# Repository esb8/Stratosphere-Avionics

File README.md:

# Stratosphere
Stratosphere is a highly **versatile** avionics stack designed for a variety of **Remote-Controlled** (RC) vehicles such as planes, model rockets, and drones. Stratosphere is designed for *verstaility*, allowing for usage as a standalone stack and alongside off the shelf modules (VTX, GPS, etc), servos and ESCs. 

## Features
- **Flight Computer**
  - 6-axis IMU (ICM-42605)
  - High Precision Barometer (BMP388)
  - 915MHz LoRa Transciever (ELRS compatible)
  - 4 UART Outputs
  - 8 PWM capable pins
  - 4 PWM/Motor control pins (4-in-1 ESC compatible) 
  - STM32F405
  - USB-C programming
- **Power Management Unit**
  - 2-4S LiPo (7.4V-14.8V)
  - 3.3V 3A (3+ outputs)
  - 5V 3A (3+ outputs)
  - Compact + Affordable
  - XT60

## Media

**Power Management Board**

## Future Deliveries
- Update PMU connector amount (5V 3 pin to 5 pin) (4 servos + VTX).
- Power ORING/multiplexer circuit on FC.
- Layout FC
- Current Calcs

## License

This project is released under the MIT License. All design files, including schematics, PCB layouts, and firmware are open source and available for personal and commercial use with attribution.

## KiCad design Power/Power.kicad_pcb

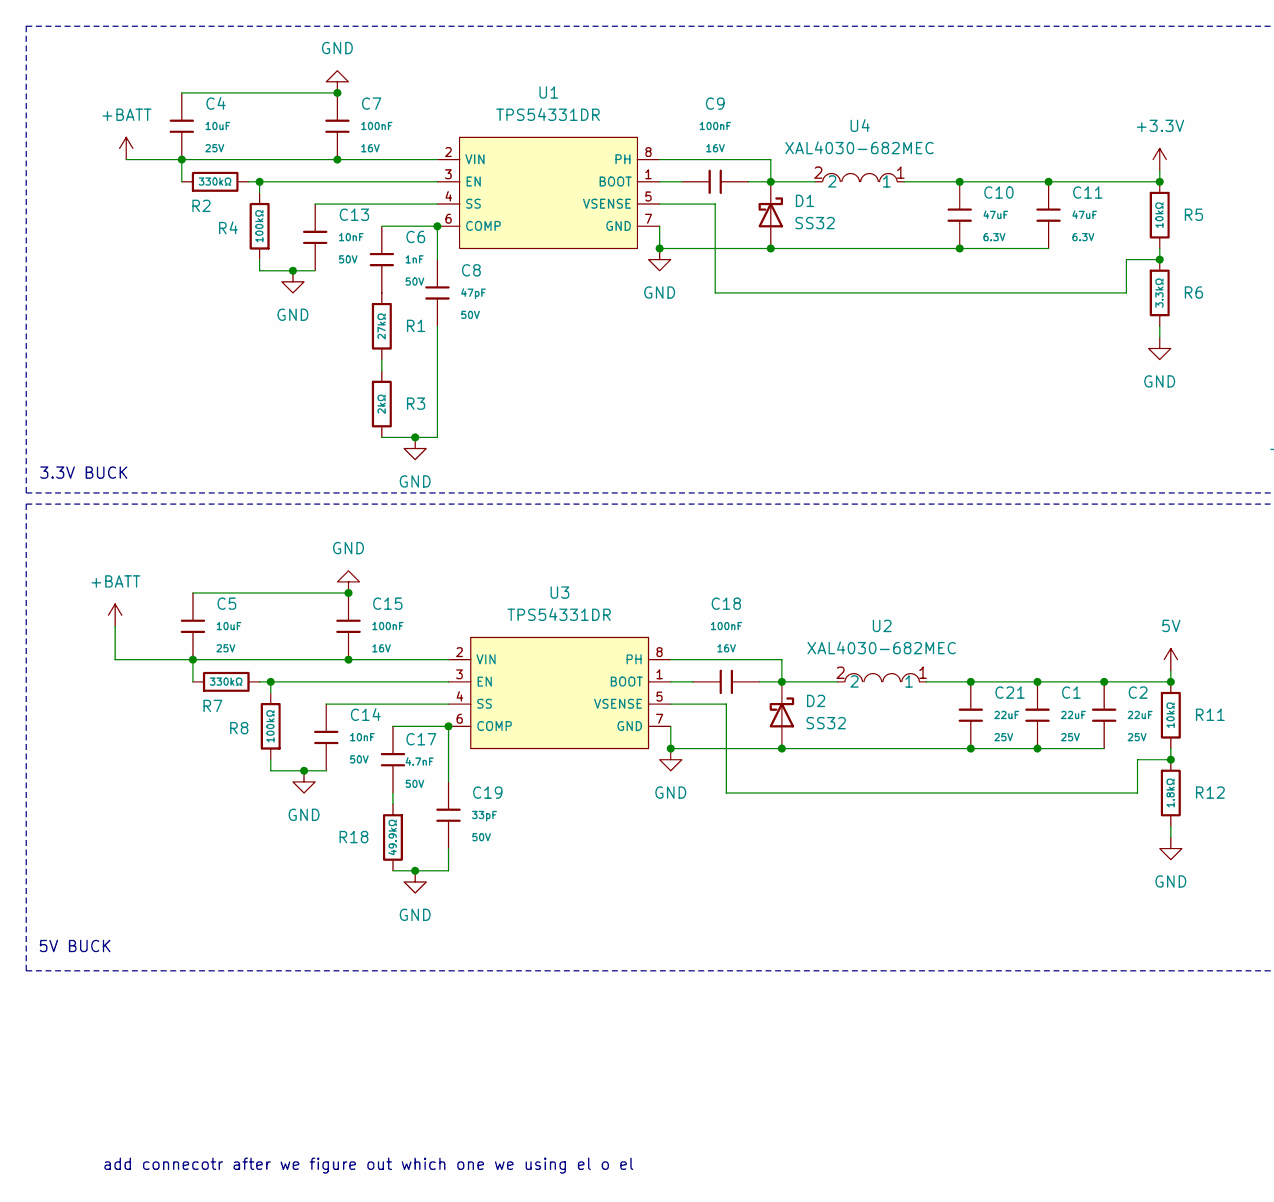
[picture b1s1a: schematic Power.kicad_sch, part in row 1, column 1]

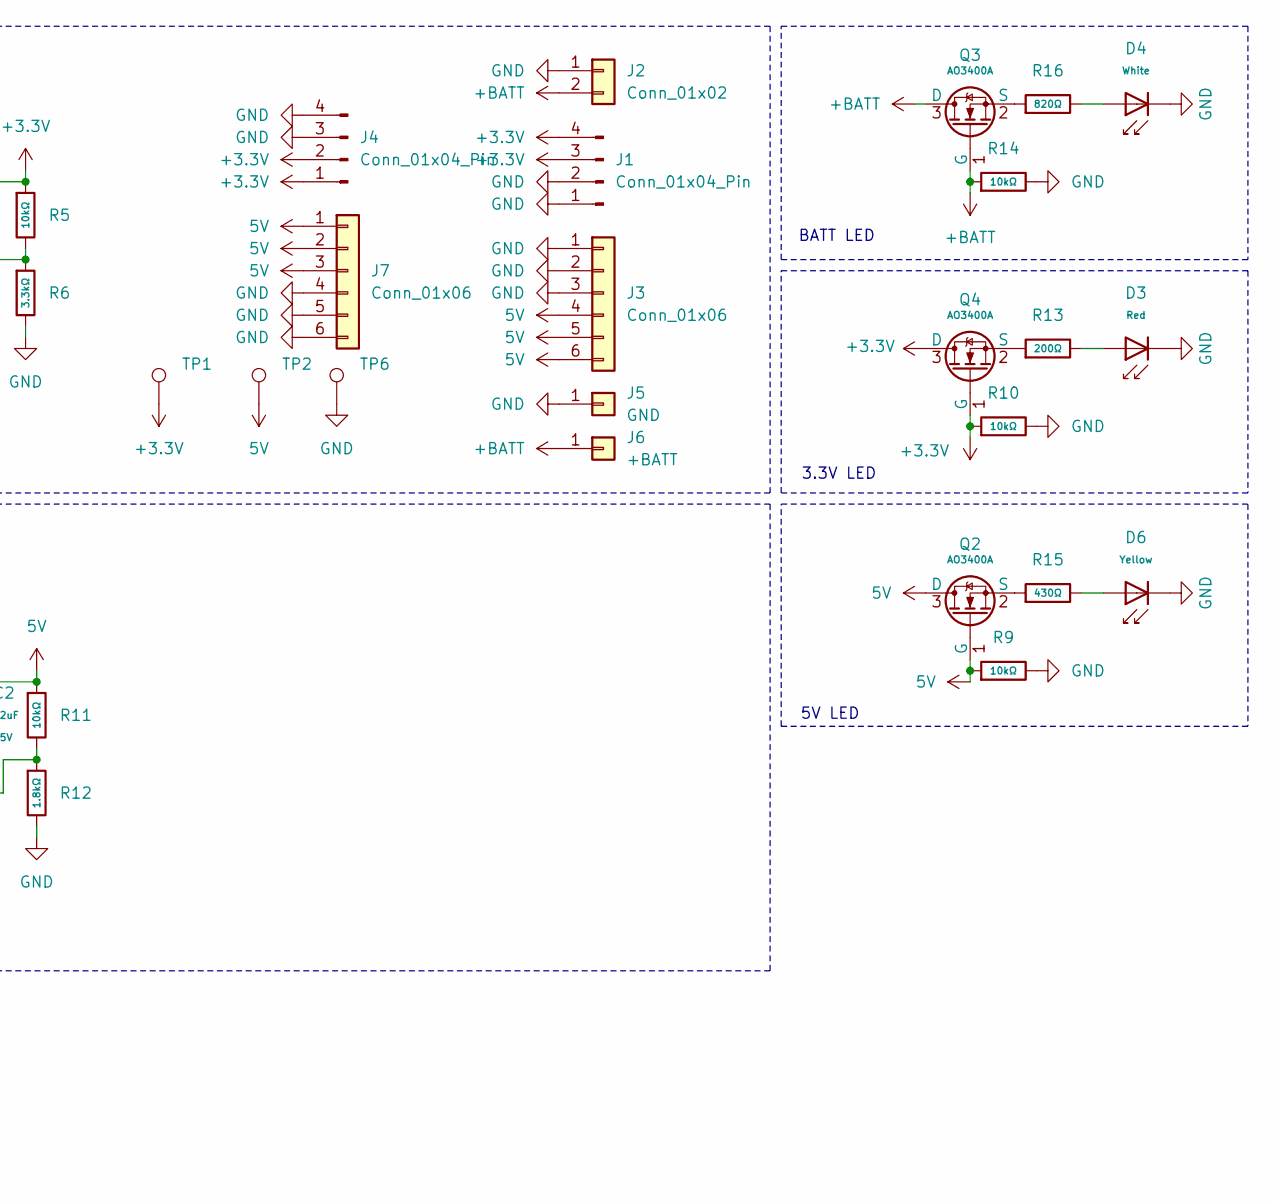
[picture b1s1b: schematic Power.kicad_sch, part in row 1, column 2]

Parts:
C1, C2, C21: 22uF; C_0805; Voltage Rated 25V; Tolerance ±20%; Part CL21A226MAQNNNE; LCSC C45783
C4, C5: 10uF; C_0603; Voltage Rated 25V; Tolerance ±20%; Part CL10A106MA8NRNC; LCSC C96446
C6: 1nF; C_0402; Voltage Rated 50V; Tolerance ±10%; Part 0402B102K500NT; LCSC C1523
C7, C9, C15, C18: 100nF; C_0402; Voltage Rated 16V; Tolerance ±10%; Part CL05B104KO5NNNC; LCSC C1525
C8: 47pF; C_0402; Voltage Rated 50V; Tolerance ±5%; Part 0402CG470J500NT; LCSC C1567
C10, C11: 47uF; C_0805; Voltage Rated 6.3V; Tolerance ±20%; Part CL21A476MQYNNNE; LCSC C16780
C13, C14: 10nF; C_0402; Voltage Rated 50V; Tolerance ±10%; Part CL05B103KB5NNNC; LCSC C15195
C17: 4.7nF; C_0402; Voltage Rated 50V; Tolerance ±10%; Part 0402B472K500NT; LCSC C1538
C19: 33pF; C_0402; Voltage Rated 50V; Tolerance ±5%; Part 0402CG330J500NT; LCSC C1562
D1, D2: SS32; D_SMA
D3: Red; D_0603; Part KT-0603R; LCSC C2286
D4: White; D_0603; Part KT-0603W; LCSC C2290
D6: Yellow; D_0603; Forward Voltage (VF) 1.6V~2.6V; Part NCD0603Y2; LCSC C89811
J1, J4: Conn_01x04_Pin; JST_GH_SM04B-GHS-TB_1x04-1MP_P1.25mm_Horizontal
J2: Conn_01x02; AMASS_XT30UPB-M_1x02_P5.0mm_Vertical
J3, J7: Conn_01x06; JST_GH_SM06B-GHS-TB_1x06-1MP_P1.25mm_Horizontal
J5: GND; TestPoint_Pad_2.5x2.5mm
J6: +BATT; TestPoint_Pad_2.5x2.5mm
Q2, Q3, Q4: AO3400A; Q_SOT-23; Part AO3400A; LCSC C20917
R1: 27kΩ; R_0402; Overload Voltage (Max) 50V; Tolerance ±1%; Part 0402WGF2702TCE; LCSC C25771
R2, R7: 330kΩ; R_0402; Overload Voltage (Max) 50V; Tolerance ±1%; Part 0402WGF3303TCE; LCSC C25778
R3: 2kΩ; R_0402; Overload Voltage (Max) 50V; Tolerance ±1%; Part 0402WGF2001TCE; LCSC C4109
R4, R8: 100kΩ; R_0402; Overload Voltage (Max) 50V; Tolerance ±1%; Part 0402WGF1003TCE; LCSC C25741
R5, R9, R10, R11, R14: 10kΩ; R_0402; Overload Voltage (Max) 50V; Tolerance ±1%; Part 0402WGF1002TCE; LCSC C25744
R6: 3.3kΩ; R_0402; Overload Voltage (Max) 50V; Tolerance ±1%; Part 0402WGF3301TCE; LCSC C25890
R12: 1.8kΩ; R_0603; Overload Voltage (Max) 75V; Tolerance ±1%; Part 0603WAF1801T5E; LCSC C4177
R13: 200Ω; R_0402; Overload Voltage (Max) 50V; Tolerance ±1%; Part 0402WGF2000TCE; LCSC C25087
R15: 430Ω; R_0603; Overload Voltage (Max) 75V; Tolerance ±1%; Part 0603WAF4300T5E; LCSC C23170
R16: 820Ω; R_0603; Overload Voltage (Max) 75V; Tolerance ±1%; Part 0603WAF8200T5E; LCSC C23253
R18: 49.9kΩ; R_0402; Overload Voltage (Max) 50V; Tolerance ±1%; Part 0402WGF4992TCE; LCSC C25897
TP1, TP2, TP6: TestPoint; TestPoint_Pad_2.0x2.0mm
U1, U3: TPS54331DR; SOIC-8_L5.0-W4.0-P1.27-LS6.0-BL; Output Voltage 0.8V~25V; Input Voltage 3.5V~28V; Part TPS54331DR; LCSC C9865
U2, U4: XAL4030-682MEC; IND-SMD_L4.0-W4.0_XAL4030-682MEC; LCSC Part C3040663

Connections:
5V: C1.1, C2.1, C21.1, J3.4, J3.5, J3.6, J7.1, J7.2, J7.3, Q2.1 (G), Q2.3 (D), R9.1, R11.1, TP2.1, U2.1
+3.3V: C10.1, C11.1, J1.3, J1.4, J4.1, J4.2, Q4.1 (G), Q4.3 (D), R5.1, R10.1, TP1.1, U4.1
+BATT: C4.1, C5.1, C7.2, C15.2, J2.2, J6.1, Q3.1 (G), Q3.3 (D), R2.1, R7.1, R14.1, U1.2 (VIN), U3.2 (VIN)
GND: C1.2, C2.2, C4.2, C5.2, C7.1, C8.2, C10.2, C11.2, C13.2, C14.2, C15.1, C19.2, C21.2, D1.2 (A), D2.2 (A), D3.1, D4.1, D6.1, J1.1, J1.2, J2.1, J3.1, J3.2, J3.3, J4.3, J4.4, J5.1, J7.4, J7.5, J7.6, R3.2, R4.1, R6.2, R8.1, R9.2, R10.2, R12.2, R14.2, R18.2, TP6.1, U1.7 (GND), U3.7 (GND)
unnamed: C6.2, R1.1
unnamed: C17.2, R18.1
unnamed: C9.2, D1.1 (K), U1.8 (PH), U4.2
unnamed: C18.2, D2.1 (K), U2.2, U3.8 (PH)
unnamed: D3.2, R13.2
unnamed: D4.2, R16.2
unnamed: D6.2, R15.2
unnamed: Q2.2 (S), R15.1
unnamed: Q3.2 (S), R16.1
unnamed: Q4.2 (S), R13.1
unnamed: R1.2, R3.1
unnamed: C9.1, U1.1 (BOOT)
unnamed: C6.1, C8.1, U1.6 (COMP)
unnamed: R2.2, R4.2, U1.3 (EN)
unnamed: C13.1, U1.4 (SS)
unnamed: R5.2, R6.1, U1.5 (VSENSE)
unnamed: C18.1, U3.1 (BOOT)
unnamed: C17.1, C19.1, U3.6 (COMP)
unnamed: R7.2, R8.2, U3.3 (EN)
unnamed: C14.1, U3.4 (SS)
unnamed: R11.2, R12.1, U3.5 (VSENSE)

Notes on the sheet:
BATT LED
5V LED
3.3V BUCK
add connecotr after we figure out which one we using el o el
5V BUCK
3.3V LED

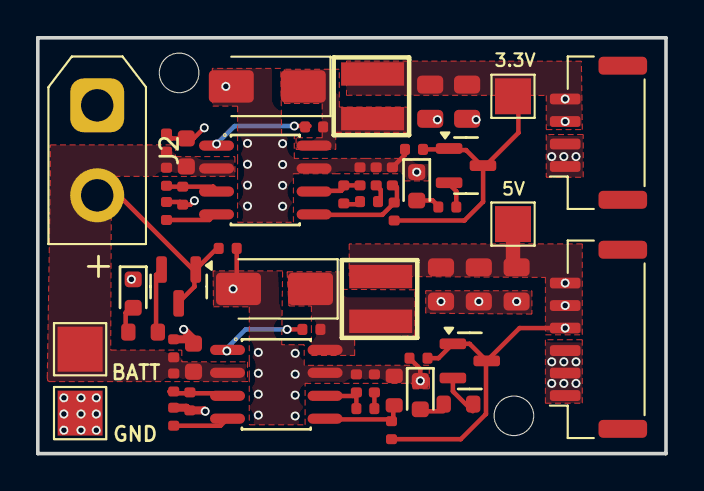
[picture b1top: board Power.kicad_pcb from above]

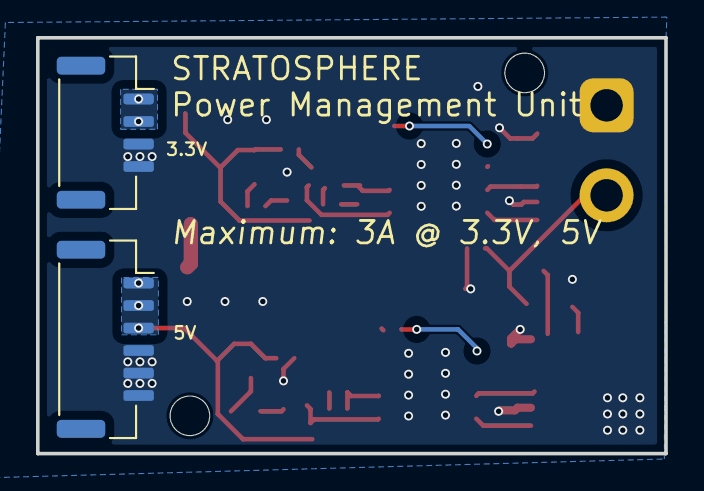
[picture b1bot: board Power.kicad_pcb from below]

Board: 2 copper layers, 34.9 x 23.1 mm, 55 parts (2 on the bottom side), 25 nets.

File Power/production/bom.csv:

Designator,Footprint,Quantity,Value,LCSC Part #
"C1, C2, C21",C_0805,3,22uF,C45783
"C10, C11",C_0805,2,47uF,C16780
"C13, C14",C_0402,2,10nF,C15195
"C15, C18, C7, C9",C_0402,4,100nF,C1525
C17,C_0402,1,4.7nF,C1538
C19,C_0402,1,33pF,C1562
"C4, C5",C_0603,2,10uF,C96446
C6,C_0402,1,1nF,C1523
C8,C_0402,1,47pF,C1567
"D1, D2",D_SMA,2,SS32,
D3,D_0603,1,Red,C2286
D4,D_0603,1,White,C2290
D6,D_0603,1,Yellow,C89811
J1,JST_GH_SM04B-GHS-TB_1x04-1MP_P1.25mm_Horizontal,1,Conn_01x04_Pin,
J2,AMASS_XT30UPB-M_1x02_P5.0mm_Vertical,1,Conn_01x02,
J3,JST_GH_SM06B-GHS-TB_1x06-1MP_P1.25mm_Horizontal,1,Conn_01x06,
J5,TestPoint_Pad_2.0x2.0mm,1,GND,
J6,TestPoint_Pad_2.0x2.0mm,1,+BATT,
"Q2, Q3, Q4",Q_SOT-23,3,AO3400A,C20917
R1,R_0402,1,27kΩ,C25771
"R10, R11, R14, R5, R9",R_0402,5,10kΩ,C25744
R12,R_0603,1,1.8kΩ,C4177
R13,R_0402,1,200Ω,C25087
R15,R_0603,1,430Ω,C23170
R16,R_0603,1,820Ω,C23253
R18,R_0402,1,49.9kΩ,C25897
"R2, R7",R_0402,2,330kΩ,C25778
R3,R_0402,1,2kΩ,C4109
"R4, R8",R_0402,2,100kΩ,C25741
R6,R_0402,1,3.3kΩ,C25890
"TP1, TP2, TP3, TP4, TP5, TP6",TestPoint_Pad_1.5x1.5mm,6,TestPoint,
"U1, U3",SOIC-8_L5.0-W4.0-P1.27-LS6.0-BL,2,TPS54331DR,C9865
"U2, U4",IND-SMD_L4.0-W4.0_XAL4030-682MEC,2,XAL4030-682MEC,C3040663

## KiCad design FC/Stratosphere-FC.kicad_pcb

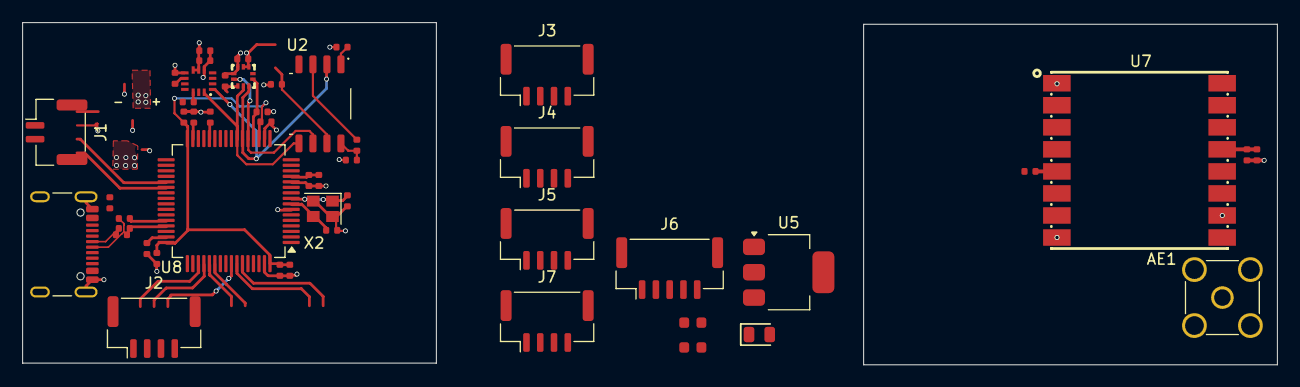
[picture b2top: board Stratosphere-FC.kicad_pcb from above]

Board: 2 copper layers, 113.9 x 31.1 mm, 49 parts (0 on the bottom side), 35 nets.

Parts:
AE1: 915MHZ Antenna; SMA_Amphenol_901-144_Vertical
C1, C2, C6, C12, C16, C17, C19, C22, C23, C28: 100nF; C_0402
C3: 10uF; C_0402
C4, C5: 22uF; C_0603
C7, C13, C14: 2.2uF; C_0402
C8: 10nF; C_0402
C24: 4.7uF; C_0402
C30: 1uF; C_0402
C32, C33: 20pF; C_0402
D3: Green; D_0805
J1: Connector; JST_GH_BM02B-GHS-TBT_1x02-1MP_P1.25mm_Vertical
J2, J3, J4, J5, J7: Conn_01x04; JST_GH_BM04B-GHS-TBT_1x04-1MP_P1.25mm_Vertical
J6: Conn_01x05; JST_GH_BM05B-GHS-TBT_1x05-1MP_P1.25mm_Vertical
P2: USB_C_Plug_USB2.0; USB_C_Receptacle_GCT_USB4105-xx-A_16P_TopMnt_Horizontal
R1, R3, R4, R7, R10, R12, R15, R17: 5.1kΩ; R_0402
R9, R16: 22Ω; R_0402
R11: 200Ω; R_0402
U1: ICM-42605; LGA-14_L3.0-W2.5-P0.50-TL
U2: W25Q16JVSS; SOIC-8_5.3x5.3mm_P1.27mm
U3: BMP388; SENSORM-SMD_BMP388
U5: AMS1117; SOT-223-3_TabPin2
U7: 915MHz; COMM-SMD_LORA1276-C1-915MHZ
U8: STM32F405RGTx; LQFP-64_10x10mm_P0.5mm
X2: Shenzhen SCTF Elec SX2B12.000F1010F30; Crystal_SMD_2520-4Pin_2.5x2.0mm

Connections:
+3.3V: C1.2, C2.1, C3.1, C4.1, C6.2, C7.1, C8.2, C12.1, C28.1, J1.1, J3.3, J4.3, J5.3, J6.4, R3.2, R4.2, R7.2, R10.1, R11.1, R12.1, R15.1, U1.5 (VDDIO), U1.8 (VDD), U2.8 (VCC), U3.1 (VDDIO), U3.10 (VDD), U5.2 (VO), U7.13 (VCC)
+5V: C5.1, P2.A4 (VBUS), P2.A9 (VBUS), P2.B4 (VBUS), P2.B9 (VBUS), U5.3 (VI)
/BOOT1: R17.1, U8.28 (PB2)
/OSC_IN: C32.1, U8.6 (PH1), U8.8 (PC0), X2.3 (OSC)
/OSC_OUT: C33.2, U8.5 (PH0), U8.9 (PC1), X2.1 (OSC)
/SPI1_MISO: U1.1 (AP_SDO/AP_AD0), U2.2 (DO/IO_{1}), U3.5 (SDO), U8.22 (PA6)
/SPI1_MOSI: U1.14 (AP_SDA/AP_SDIO/AP_SDI), U2.5 (DI/IO_{0}), U3.4 (SDI), U8.23 (PA7)
/SPI1_NSS: R15.2, U3.6 (CSB), U8.20 (PA4)
/SPI1_SCK: U1.13 (AP_SCL/AP_SCLK), U2.6 (CLK), U3.2 (SCK), U8.21 (PA5)
/SPI2_NSS: R12.2, U1.12 (AP_CS)
/SPI3_MISO: J6.2, U7.2 (MISO), U8.52 (PC11)
/SPI3_MOSI: J6.3, U7.3 (MOSI), U8.57 (PB5)
/SPI3_NSS: R10.2, U7.5 (NSS)
/SPI3_SCK: J6.1, U7.4 (SCK), U8.51 (PC10)
/SPI5_NSS: R7.1, U2.1 (~CS)
/UART5_RX: J5.1, U8.53 (PC12)
/UART5_TX: J5.2, U8.54 (PD2)
/USART1_RX: J4.2, U8.59 (PB7)
/USART1_TX: J4.1, U8.58 (PB6)
/USART6_RX: J3.2, U8.38 (PC7)
/USART6_TX: J3.1, U8.37 (PC6)
/USB_FS_DN: P2.A7 (D-), R16.2
/USB_FS_DP: P2.A6 (D+), R9.2
GND: C1.1, C2.2, C3.2, C4.2, C5.2, C6.1, C7.2, C8.1, C12.2, C13.2, C14.2, C16.2, C17.2, C19.2, C22.2, C23.2, C24.2, C28.2, C30.2, C32.2, C33.1, D3.1, J1.2, J3.4, J4.4, J5.4, J6.5, P2.A1 (GND), P2.A12 (GND), P2.B1 (GND), P2.B12 (GND), P2.S1 (SHIELD), R1.1, R17.2, U1.6 (GND), U1.7 (RESV), U1.9 (INT2/FSYNC), U2.4 (GND), U3.3 (VSS), U3.8 (VSS), U3.9 (VSS), U5.1 (ADJ), U7.1 (GND), U7.8 (GND), U7.10 (GND), U8.12 (VSSA), U8.18 (VSS), U8.63 (VSS), X2.2 (GND), X2.4 (GND)
unnamed: AE1.1 (A), U7.9 (ANT)
unnamed: C16.1, C17.1, C19.1, C22.1, C24.1, U8.19 (VDD), U8.32 (VDD), U8.48 (VDD), U8.64 (VDD)
unnamed: D3.2, R11.2
unnamed: P2.A5 (CC), R1.2
unnamed: R4.1, U2.7 (~HOLD/~RESET/IO_{3})
unnamed: R3.1, U2.3 (~WP/IO_{2})
unnamed: R16.1, U8.44 (PA11)
unnamed: R9.1, U8.45 (PA12)
unnamed: C13.1, U8.31 (VCAP_1)
unnamed: C14.1, U8.47 (VCAP_2)
unnamed: C23.1, C30.1, U8.13 (VDDA)

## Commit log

2026-01-15 Feat: Initialized Repo with FC schematic and PCB
2026-01-25 Feat: Addition of Power Module Schematic PCB
2026-01-27 Add README.md for Stratosphere avionics stack
    Introduced a README file detailing the Stratosphere avionics stack, its features, and licensing information.
2026-01-27 Update supported RC vehicles in README description
    Removed 'cars' from the list of supported RC vehicles in the README.
2026-02-01 fix: updated connector, horzontal to vertical
2026-02-01 Completed pin mapping of STM32
2026-02-01 Update README with Media and Future Deliveries sections
    Added sections for Media and Future Deliveries in README.
2026-02-01 feat: Added mounting holes, text and more connectors for PMU
